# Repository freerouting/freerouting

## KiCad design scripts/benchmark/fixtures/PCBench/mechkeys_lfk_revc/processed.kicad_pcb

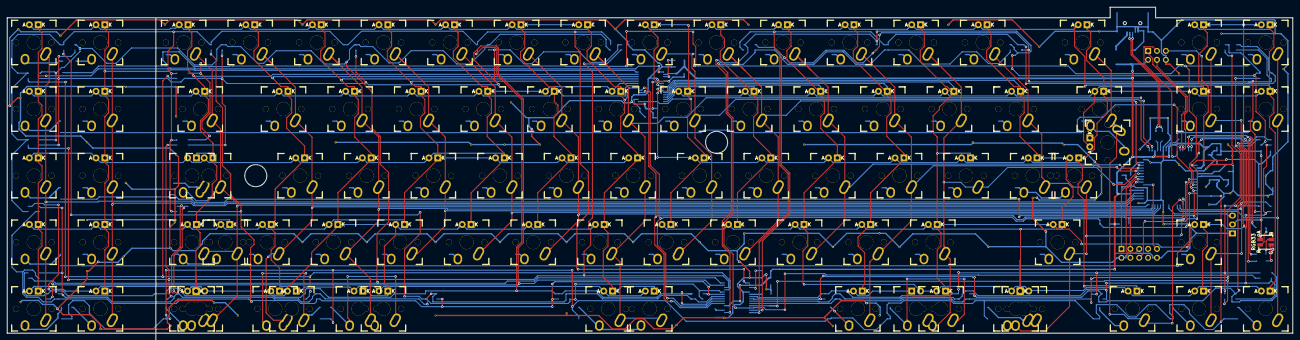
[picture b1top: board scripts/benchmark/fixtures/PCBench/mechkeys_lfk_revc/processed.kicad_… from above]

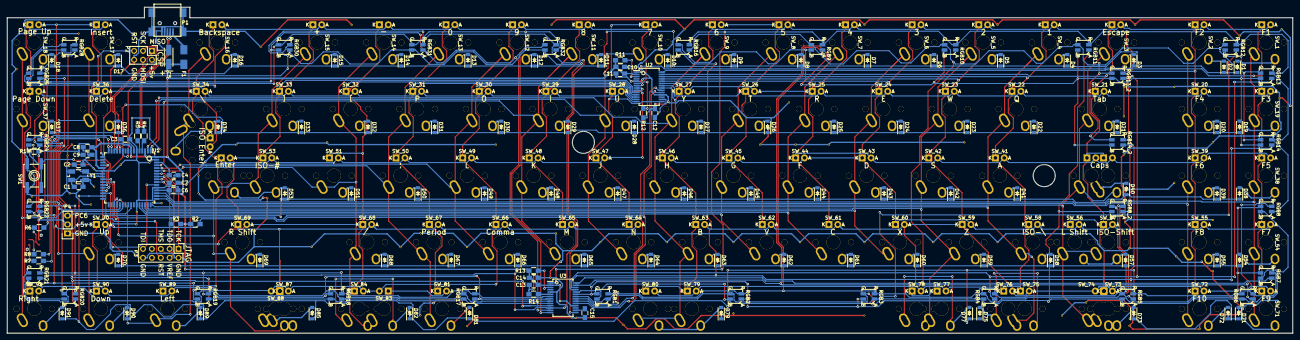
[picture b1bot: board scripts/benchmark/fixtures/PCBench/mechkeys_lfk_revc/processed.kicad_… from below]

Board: 2 copper layers, 367.8 x 93.2 mm, 238 parts (146 on the bottom side), 172 nets.

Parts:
C1, C2: 18pF; C_0805_HandSoldering
C3, C6, C7, C8, C9, C11, C12, C14, C15: 0.1µF; C_0805_HandSoldering
C4, C10, C13: 1µF; C_0805_HandSoldering
C5: 4.7µF; TantalC_SizeA_EIA-3216_HandSoldering
D1, D2, D3, D4, D5, D6, D7, D8, D9, D10, D11, D12, D13, D14, D15, D16, D17, D18, D19, D20, D21, D22, D23, D24, D25, D26, D27, D28, D29, D30, D31, D32, D33, D34, D36, D37, D38, D39, D40, D41, D42, D43, D44, D45, D46, D47, D48, D49, D50, D51, D53, D54, D55, D57, D58, D59, D60, D61, D62, D63, D64, D65, D66, D67, D68, D69, D70, D71, D72, D73, D75, D77, D79, D81, D82, D85, D89, D90, D91: D; SOD-123
F1: FP_Small; Fuse_SMD1206_HandSoldering
P1: USB_B; USB_Mini-B
P2: CONN_02X03; Pin_Header_Straight_2x03
P3: CONN_02X05; Pin_Header_Straight_2x05
P4: CONN_01X03; Pin_Header_Straight_1x03
R1: 10kΩ; R_0805_HandSoldering
R2, R3: 4.7kΩ; R_0805_HandSoldering
R4, R5: 22Ω; R_0805_HandSoldering
R6: 150; R_0805_HandSoldering
R7, R8: 120; R_0805_HandSoldering
R11, R13: 10KΩ; R_0805_HandSoldering
R12, R14: 20KΩ; R_0805_HandSoldering
RGB1, RGB2, RGB3, RGB4, RGB5, RGB6, RGB7, RGB8, RGB8_2, RGB9, RGB10, RGB11, RGB12, RGB13, RGB13_2, RGB14, RGB14_2, RGB16, RGB17, RGB18, RGB19, RGB20, RGB21, RGB22, RGB24, RGB25, RGB28, RGB30, RGB31, RGB32: Led_RGB_CA; SMP4-RGB
RGB33: Led_RGB_CA; SMP4-RGB-PIPE
STA: Stabilizer; CHERRY_PCB_200_STABILIZER_OUTLINE
STA_2: Stabilizer; CHERRY_PCB_200_STABILIZER_OUTLINE
SW1: SW_PUSH; SW_SPST_EVQP0
SW_1, SW_2, SW_3, SW_4, SW_5, SW_6, SW_7, SW_8, SW_9, SW_10, SW_11, SW_12, SW_13, SW_14, SW_15, SW_16, SW_17, SW_18, SW_19, SW_20, SW_21, SW_22, SW_23, SW_24, SW_25, SW_26, SW_27, SW_28, SW_29, SW_30, SW_31, SW_32, SW_33, SW_34, SW_35, SW_36, SW_37, SW_38, SW_39, SW_40, SW_40_2, SW_41, SW_42, SW_43, SW_44, SW_45, SW_46, SW_47, SW_48, SW_49, SW_50, SW_51, SW_52, SW_53, SW_54, SW_55, SW_56, SW_57, SW_58, SW_59, SW_60, SW_61, SW_62, SW_63, SW_64, SW_65, SW_66, SW_67, SW_68, SW_69, SW_70, SW_71, SW_72, SW_73, SW_75, SW_76, SW_77, SW_78, SW_79, SW_80, SW_81, SW_84, SW_87, SW_89, SW_90, SW_91: MX_LED; MXALPS
SW_74, SW_83, SW_88: MX_LED; MXALPS_REVERSE_LED
U1: AT90USB1286; TQFP-64_14x14mm_Pitch0.8mm
U2, U3: IS31FL3731; SSOP-28_5.3x10.2mm_Pitch0.65mm
Y1: 16Mhz; Crystal_SMD_5032_4Pads

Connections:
+5V: C5.1, C6.1, C7.1, C8.1, C9.1, C10.1, C11.1, C13.1, C14.1, F1.2, P2.2, P3.4, P4.2, R1.1, R2.1, R3.1, R11.2, R13.2, RGB33.1, U1.3, U1.8, U1.21, U1.52, U1.64, U2.2, U3.2, U3.18
AUDIO: P4.3, U1.41
C1: SW_1.SW1, SW_19.SW1, SW_38.SW1, SW_54.SW1, SW_71.SW1, U1.51
C2: SW_2.SW1, SW_20.SW1, SW_39.SW1, SW_55.SW1, SW_72.SW1, U1.50
C3: SW_3.SW1, SW_21.SW1, SW_40.SW1, SW_40_2.SW2, SW_56.SW1, SW_57.SW1, SW_73.SW1, SW_74.SW1, U1.49
C4: SW_4.SW1, SW_22.SW1, SW_41.SW1, SW_58.SW1, SW_75.SW1, SW_76.SW2, U1.48
C5: SW_5.SW1, SW_23.SW1, SW_42.SW1, SW_59.SW1, SW_77.SW1, SW_78.SW2, U1.47
C6: SW_6.SW1, SW_24.SW1, SW_43.SW1, SW_60.SW1, U1.46
C7: SW_7.SW1, SW_25.SW1, SW_44.SW1, SW_61.SW1, U1.45
C8: SW_8.SW1, SW_26.SW1, SW_45.SW1, SW_62.SW1, U1.44
C9: SW_9.SW1, SW_27.SW1, SW_46.SW1, SW_63.SW1, SW_79.SW1, SW_80.SW1, U1.1
C10: SW_10.SW1, SW_28.SW1, SW_47.SW1, SW_64.SW1, U1.2
C11: SW_11.SW1, SW_29.SW1, SW_48.SW1, SW_65.SW1, U1.61
C12: SW_12.SW1, SW_30.SW1, SW_49.SW1, SW_66.SW1, U1.60
C13: SW_13.SW1, SW_31.SW1, SW_50.SW1, SW_67.SW1, SW_81.SW1, U1.59
C14: SW_14.SW1, SW_32.SW1, SW_51.SW1, SW_68.SW1, SW_83.SW1, SW_84.SW2, U1.58
C15: SW_15.SW1, SW_33.SW1, SW_52.SW1, SW_53.SW1, SW_69.SW1, SW_87.SW2, SW_88.SW2, U1.35
C16: SW_16.SW1, SW_34.SW1, SW_35.SW1, SW_89.SW1, U1.36
C17: SW_17.SW1, SW_36.SW1, SW_70.SW1, SW_90.SW1, U1.37
C18: SW_18.SW1, SW_37.SW1, SW_91.SW1, U1.38
D+: R5.1, U1.5
D-: R4.1, U1.4
GND: C1.2, C2.2, C3.2, C4.2, C5.2, C6.2, C7.2, C8.2, C9.2, C10.2, C11.2, C12.2, C13.2, C14.2, C15.2, P1.4, P1.5, P1.6, P2.6, P3.2, P3.10, P4.1, R12.2, R14.2, SW1.1, U1.6, U1.22, U1.43, U1.53, U1.63, U2.5, U2.18, U3.5, Y1.3
LED_SCL: R2.2, U1.25, U2.20, U3.20
LED_SDA: R3.2, U1.26, U2.19, U3.19
L_CA1: SW_1.A, SW_2.A, SW_3.A, SW_4.A, SW_5.A, SW_6.A, SW_7.A, SW_8.A, SW_9.K, SW_27.K, SW_46.K, SW_63.K, SW_79.K, SW_80.K, U2.21
L_CA2: SW_8.K, SW_9.A, SW_19.A, SW_20.A, SW_21.A, SW_22.A, SW_23.A, SW_24.A, SW_25.A, SW_26.K, SW_45.K, SW_62.K, U2.22
L_CA3: SW_7.K, SW_25.K, SW_26.A, SW_27.A, SW_38.A, SW_39.A, SW_40.A, SW_40_2.A, SW_41.A, SW_42.A, SW_43.A, SW_44.K, SW_61.K, U2.23
L_CA4: SW_6.K, SW_24.K, SW_43.K, SW_44.A, SW_45.A, SW_46.A, SW_54.A, SW_55.A, SW_56.A, SW_57.A, SW_58.A, SW_59.A, SW_60.K, U2.24
L_CA5: SW_5.K, SW_23.K, SW_42.K, SW_59.K, SW_60.A, SW_61.A, SW_62.A, SW_63.A, SW_71.A, SW_72.A, SW_73.A, SW_74.A, SW_75.A, SW_76.A, SW_77.K, SW_78.K, U2.25
L_CA6: SW_4.K, SW_22.K, SW_41.K, SW_58.K, SW_75.K, SW_76.K, SW_77.A, SW_78.A, SW_79.A, SW_80.A, U2.26
L_CA7: SW_3.K, SW_21.K, SW_40.K, SW_40_2.K, SW_56.K, SW_57.K, SW_73.K, SW_74.K, U2.27
L_CA8: SW_2.K, SW_20.K, SW_39.K, SW_55.K, SW_72.K, U2.28
L_CA9: SW_1.K, SW_19.K, SW_38.K, SW_54.K, SW_71.K, U2.1
L_CB1: SW_10.A, SW_11.A, SW_12.A, SW_13.A, SW_14.A, SW_15.A, SW_16.A, SW_17.A, SW_18.K, SW_37.K, SW_91.K, U2.7
L_CB2: SW_17.K, SW_18.A, SW_28.A, SW_29.A, SW_30.A, SW_31.A, SW_32.A, SW_33.A, SW_34.A, SW_35.A, SW_36.K, SW_70.K, SW_90.K, U2.8
L_CB3: SW_16.K, SW_34.K, SW_35.K, SW_36.A, SW_37.A, SW_47.A, SW_48.A, SW_49.A, SW_50.A, SW_51.A, SW_52.K, SW_53.A, SW_89.K, U2.9
L_CB4: SW_15.K, SW_33.K, SW_52.A, SW_53.K, SW_64.A, SW_65.A, SW_66.A, SW_67.A, SW_68.A, SW_69.K, SW_87.K, SW_88.K, U2.10
L_CB5: SW_14.K, SW_32.K, SW_51.K, SW_68.K, SW_69.A, SW_70.A, SW_81.A, SW_83.K, SW_84.K, U2.11
L_CB6: SW_13.K, SW_31.K, SW_50.K, SW_67.K, SW_81.K, U2.12
L_CB7: SW_12.K, SW_30.K, SW_49.K, SW_66.K, SW_83.A, SW_84.A, SW_87.A, SW_88.A, SW_89.A, SW_90.A, SW_91.A, U2.13
L_CB8: SW_11.K, SW_29.K, SW_48.K, SW_65.K, U2.14
L_CB9: SW_10.K, SW_28.K, SW_47.K, SW_64.K, U2.15
MISO: P2.1, U1.13
MOSI: P2.4, U1.12
unnamed: C1.1, U1.24, Y1.1
unnamed: C2.1, U1.23, Y1.2
unnamed: C3.1, U1.7
unnamed: C4.1, U1.62
unnamed: C12.1, U2.16
unnamed: C15.1, U3.16
unnamed: D1.2, SW_1.SW2
unnamed: D2.2, SW_2.SW2
unnamed: D3.2, SW_3.SW2
unnamed: D4.2, SW_4.SW2
unnamed: D5.2, SW_5.SW2
unnamed: D6.2, SW_6.SW2
unnamed: D7.2, SW_7.SW2
unnamed: D8.2, SW_8.SW2
unnamed: D9.2, SW_9.SW2
unnamed: D10.2, SW_10.SW2
unnamed: D11.2, SW_11.SW2
unnamed: D12.2, SW_12.SW2
unnamed: D13.2, SW_13.SW2
unnamed: D14.2, SW_14.SW2
unnamed: D15.2, SW_15.SW2
unnamed: D16.2, SW_16.SW2
unnamed: D17.2, SW_17.SW2
unnamed: D18.2, SW_18.SW2
unnamed: D19.2, SW_19.SW2
unnamed: D20.2, SW_20.SW2
unnamed: D21.2, SW_21.SW2
unnamed: D22.2, SW_22.SW2
unnamed: D23.2, SW_23.SW2
unnamed: D24.2, SW_24.SW2
unnamed: D25.2, SW_25.SW2
unnamed: D26.2, SW_26.SW2
unnamed: D27.2, SW_27.SW2
unnamed: D28.2, SW_28.SW2
unnamed: D29.2, SW_29.SW2
unnamed: D30.2, SW_30.SW2
unnamed: D31.2, SW_31.SW2
unnamed: D32.2, SW_32.SW2
unnamed: D33.2, SW_33.SW2
unnamed: D34.2, SW_34.SW2, SW_35.SW2
unnamed: D36.2, SW_36.SW2
unnamed: D37.2, SW_37.SW2
unnamed: D38.2, SW_38.SW2
unnamed: D39.2, SW_39.SW2
unnamed: D40.2, SW_40.SW2, SW_40_2.SW1
unnamed: D41.2, SW_41.SW2
unnamed: D42.2, SW_42.SW2
unnamed: D43.2, SW_43.SW2
unnamed: D44.2, SW_44.SW2
unnamed: D45.2, SW_45.SW2
unnamed: D46.2, SW_46.SW2
unnamed: D47.2, SW_47.SW2
unnamed: D48.2, SW_48.SW2
unnamed: D49.2, SW_49.SW2
unnamed: D50.2, SW_50.SW2
unnamed: D51.2, SW_51.SW2
unnamed: D53.2, SW_52.SW2, SW_53.SW2
unnamed: D54.2, SW_54.SW2
unnamed: D55.2, SW_55.SW2
unnamed: D57.2, SW_56.SW2, SW_57.SW2
unnamed: D58.2, SW_58.SW2
unnamed: D59.2, SW_59.SW2
unnamed: D60.2, SW_60.SW2
unnamed: D61.2, SW_61.SW2
unnamed: D62.2, SW_62.SW2
unnamed: D63.2, SW_63.SW2
unnamed: D64.2, SW_64.SW2
unnamed: D65.2, SW_65.SW2
unnamed: D66.2, SW_66.SW2
unnamed: D67.2, SW_67.SW2
unnamed: D68.2, SW_68.SW2
unnamed: D69.2, SW_69.SW2
unnamed: D70.2, SW_70.SW2
unnamed: D71.2, SW_71.SW2
unnamed: D72.2, SW_72.SW2
unnamed: D73.2, SW_73.SW2, SW_74.SW2
unnamed: D75.2, SW_75.SW2, SW_76.SW1
unnamed: D77.2, SW_77.SW2, SW_78.SW1
unnamed: D79.2, SW_79.SW2, SW_80.SW2
unnamed: D81.2, SW_81.SW2
unnamed: D82.2, SW_83.SW2, SW_84.SW1
unnamed: D85.2, SW_87.SW1, SW_88.SW1
unnamed: D89.2, SW_89.SW2
unnamed: D90.2, SW_90.SW2
unnamed: D91.2, SW_91.SW2
unnamed: F1.1, P1.1
unnamed: R6.1, RGB33.2
unnamed: R7.1, RGB33.3
unnamed: R8.1, RGB33.4
unnamed: R11.1, U2.3
unnamed: R12.1, U2.6
unnamed: R13.1, U3.3
unnamed: R14.1, U3.6
PWM_BLUE: R8.2, U1.17
PWM_GREEN: R7.2, U1.16
PWM_RED: R6.2, U1.15
R1: D1.1, D2.1, D3.1, D4.1, D5.1, D6.1, D7.1, D8.1, D9.1, D10.1, D11.1, D12.1, D13.1, D14.1, D15.1, D16.1, D17.1, D18.1, U1.27
R2: D19.1, D20.1, D21.1, D22.1, D23.1, D24.1, D25.1, D26.1, D27.1, D28.1, D29.1, D30.1, D31.1, D32.1, D33.1, D34.1, D36.1, D37.1, U1.28
R3: D38.1, D39.1, D40.1, D41.1, D42.1, D43.1, D44.1, D45.1, D46.1, D47.1, D48.1, D49.1, D50.1, D51.1, D53.1, U1.29
R4: D54.1, D55.1, D57.1, D58.1, D59.1, D60.1, D61.1, D62.1, D63.1, D64.1, D65.1, D66.1, D67.1, D68.1, D69.1, D70.1, U1.30
R5: D71.1, D72.1, D73.1, D75.1, D77.1, D79.1, D81.1, D82.1, D85.1, D89.1, D90.1, D91.1, U1.31
RESET: P2.5, P3.6, R1.2, SW1.2, U1.20
R_CA1: RGB1.2, RGB2.2, RGB3.2, RGB4.2, RGB5.2, RGB6.2, RGB7.2, RGB8.2, RGB8_2.2, RGB9.1, U3.21
R_CA2: RGB1.1, RGB2.3, RGB3.3, RGB4.3, RGB5.3, RGB6.3, RGB7.3, RGB8.3, RGB8_2.3, U3.22
R_CA3: RGB1.3, RGB2.1, RGB3.4, RGB4.4, RGB5.4, RGB6.4, RGB7.4, RGB8.4, RGB8_2.4, RGB11.1, U3.23
R_CA4: RGB1.4, RGB2.4, RGB3.1, RGB12.1, U3.24
R_CA5: RGB4.1, RGB13.1, RGB13_2.1, U3.25
R_CA6: RGB5.1, RGB14.1, RGB14_2.1, RGB16.4, U3.26
R_CA7: RGB6.1, RGB9.4, RGB10.4, RGB11.4, RGB12.4, RGB13.4, RGB13_2.4, RGB14.4, RGB14_2.4, RGB16.3, U3.27
R_CA8: RGB7.1, RGB9.3, RGB10.3, RGB11.3, RGB12.3, RGB13.3, RGB13_2.3, RGB14.3, RGB14_2.3, RGB16.1, U3.28
R_CA9: RGB8.1, RGB8_2.1, RGB9.2, RGB10.2, RGB11.2, RGB12.2, RGB13.2, RGB13_2.2, RGB14.2, RGB14_2.2, RGB16.2, U3.1
R_CB1: RGB17.2, RGB18.2, RGB19.2, RGB20.2, RGB21.2, RGB22.2, RGB24.2, RGB25.1, U3.7
R_CB2: RGB17.1, RGB18.3, RGB19.3, RGB20.3, RGB21.3, RGB22.3, RGB24.3, U3.8
R_CB3: RGB17.3, RGB18.1, RGB19.4, RGB20.4, RGB21.4, RGB22.4, RGB24.4, U3.9
R_CB4: RGB17.4, RGB18.4, RGB19.1, RGB28.1, U3.10
R_CB5: RGB20.1, U3.11
R_CB6: RGB21.1, RGB30.1, RGB31.4, RGB32.4, U3.12
R_CB7: RGB22.1, RGB25.4, RGB28.4, RGB30.4, RGB31.1, RGB32.3, U3.13
R_CB8: RGB25.3, RGB28.3, RGB30.3, RGB31.3, RGB32.1, U3.14
R_CB9: RGB24.1, RGB25.2, RGB28.2, RGB30.2, RGB31.2, RGB32.2, U3.15
SCK: P2.3, U1.11
TCK: P3.1, U1.57
TDI: P3.9, U1.54
TDO: P3.3, U1.55
TMS: P3.5, U1.56
USB+: P1.3, R5.2
USB-: P1.2, R4.2

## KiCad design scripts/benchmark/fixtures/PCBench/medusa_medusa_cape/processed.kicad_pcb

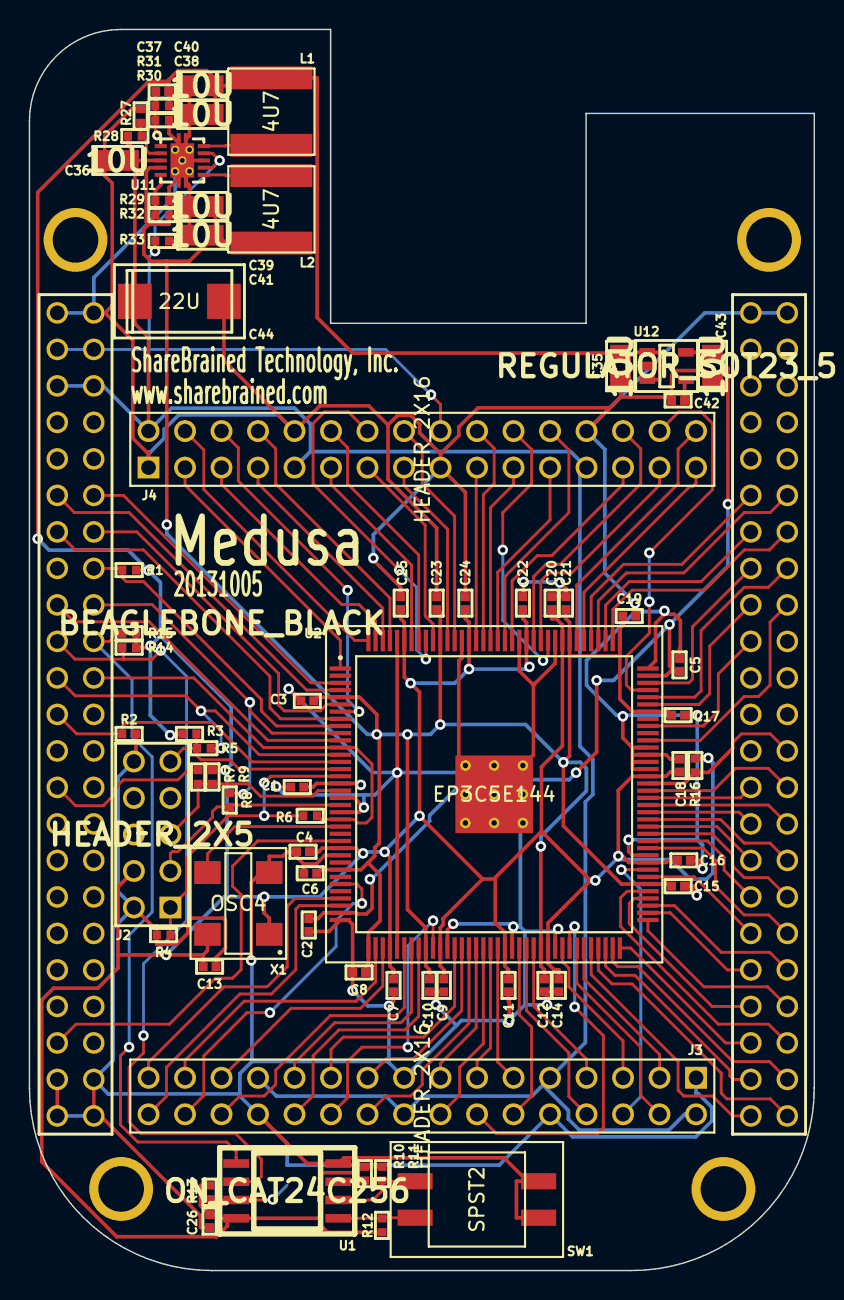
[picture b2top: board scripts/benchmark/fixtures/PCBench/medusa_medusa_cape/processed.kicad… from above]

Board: 4 copper layers, 54.6 x 86.4 mm, 73 parts (0 on the bottom side), 113 nets.

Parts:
C1, C2, C3, C4, C5, C6, C7, C8, C9, C10, C11, C12, C13, C14, C15, C16, C17, C18, C19, C20, C21, C22, C23, C24, C25, C26: 100N; IPC_CAPC1005X55N
C35, C36, C38, C39, C40, C41, C43: 10U; IPC_CAPC2012X140N
C37: 33P; IPC_CAPC1005X55N
C42: DNI; IPC_CAPC1005X55N
C44: 22U; IPC_CAPMP7343X310N
J1: BEAGLEBONE_BLACK; beaglebone_black
J2: HEADER_2X5; HEADER_5X2_TH_254
J3, J4: HEADER_2X16; HEADER_16X2_TH_254
L1, L2: 4U7; NR6028
R1, R2, R3, R9, R10, R11, R12, R13, R14, R15, R16, R28, R33: 10K; IPC_RESC1005X40N
R4: 1K; IPC_RESC1005X40N
R5, R6, R7, R8, R27: DNI; IPC_RESC1005X40N
R29, R30, R31, R32: R; IPC_RESC1005X40N
SW1: SPST2; 219-2MST
TP1, TP2: TP; TP_1MM
U1: ON_CAT24C256; IPC_SOIC127P780X205-8N
U2: EP3C5E144; QFP50P2200X2200X160-145N_ALTERA
U11: TPS62420; TI_DRC_S-PVSON-N10
U12: REGULATOR_SOT23_5; IPC_SOT95P280X110-5N
X1: OSC4; OSCSC508P500X700X180-4N

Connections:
+1.2V: C3.1, C6.1, C8.1, C10.1, C12.1, C15.1, C17.1, C19.1, C21.1, C23.1, C39.2, C41.2, L2.2, R32.2, U2.5, U2.29, U2.37, U2.45, U2.61, U2.78, U2.102, U2.109, U2.116, U2.134, U11.4
+2.5V: C2.1, C5.1, C43.1, U2.35, U2.107, U12.5
+3.3V: C1.1, C4.1, C7.1, C9.1, C11.1, C13.1, C14.1, C16.1, C18.1, C20.1, C22.1, C24.1, C25.1, C26.1, C35.1, C37.2, C38.1, C40.1, J2.4, L1.1, R1.1, R3.1, R9.1, R10.1, R11.1, R12.1, R13.1, R14.1, R15.1, R16.1, R31.2, U1.8, U2.17, U2.26, U2.40, U2.47, U2.56, U2.62, U2.81, U2.93, U2.117, U2.122, U2.130, U2.139, U12.1, U12.3, X1.1, X1.4
/FPGA/AF0: J3.3, U2.67
/FPGA/AF1: J3.4, U2.66
/FPGA/AF2: J3.5, U2.64
/FPGA/AF3: J3.7, U2.60
/FPGA/AF4: J3.8, U2.59
/FPGA/AF5: J3.11, U2.55
/FPGA/AF6: J3.12, U2.58
/FPGA/AF7: J3.13, U2.54
/FPGA/AF8: J3.15, U2.52
/FPGA/AF9: J3.16, U2.53
/FPGA/AF10: J3.19, U2.50
/FPGA/AF11: J3.20, U2.51
/FPGA/AF12: J3.21, U2.49
/FPGA/AF13: J3.23, U2.43
/FPGA/AF14: J3.24, U2.44
/FPGA/AF15: J3.27, U2.39
/FPGA/AF16: J3.28, U2.42
/FPGA/AF17: J3.29, U2.38
/FPGA/AF18: J3.31, U2.33
/FPGA/AF19: J3.32, U2.34
/FPGA/AS0: J3.6, U2.80
/FPGA/AS1: J3.14, U2.65
/FPGA/AS2: J3.22, U2.46
/FPGA/AS3: J3.30, U2.31
/FPGA/BF0: J4.3, U2.1
/FPGA/BF1: J4.4, U2.144
/FPGA/BF2: J4.5, U2.143
/FPGA/BF3: J4.7, U2.142
/FPGA/BF4: J4.8, U2.141
/FPGA/BF5: J4.11, U2.138
/FPGA/BF6: J4.12, U2.137
/FPGA/BF7: J4.13, U2.135
/FPGA/BF8: J4.15, U2.133
/FPGA/BF9: J4.16, U2.132
/FPGA/BF10: J4.19, U2.129
/FPGA/BF11: J4.20, U2.128
/FPGA/BF12: J4.21, U2.127
/FPGA/BF13: J4.23, U2.126
/FPGA/BF14: J4.24, U2.125
/FPGA/BF15: J4.27, U2.124
/FPGA/BF16: J4.28, U2.121
/FPGA/BF17: J4.29, U2.120
/FPGA/BF18: J4.31, U2.114
/FPGA/BF19: J4.32, U2.115
/FPGA/BS0: J4.6, U2.7
/FPGA/BS1: J4.14, U2.136
/FPGA/BS2: J4.22, U2.119
/FPGA/BS3: J4.30, U2.105
/FPGA/CLKOUT2: J1.B41, U2.25
/FPGA/EHRPWM1A: J1.B14, U2.6
/FPGA/EHRPWM1B: J1.B16, R1.2, U2.9
/FPGA/GPIO1_17: J1.B23, R2.1, U2.14
/FPGA/GPIO1_28: J1.B12, U2.3
/FPGA/GPIO1_29: J1.A26, R16.2, U2.92
/FPGA/GPIO2_1: J1.A18, U2.98
/FPGA/GPIO3_19: J1.B27, R7.2
/FPGA/I2C2_SCL: J1.B19, R14.2, U1.6
/FPGA/I2C2_SDA: J1.B20, R15.2, U1.5
/FPGA/LCD_DATA0: J1.A45, U2.68
/FPGA/LCD_DATA1: J1.A46, U2.69
/FPGA/LCD_DATA2: J1.A43, U2.70
/FPGA/LCD_DATA3: J1.A44, U2.71
/FPGA/LCD_DATA4: J1.A41, U2.72
/FPGA/LCD_DATA5: J1.A42, U2.77
/FPGA/LCD_DATA6: J1.A39, U2.76
/FPGA/LCD_DATA7: J1.A40, U2.73
/FPGA/LCD_DATA8: J1.A37, U2.74
/FPGA/LCD_DATA9: J1.A38, U2.75
/FPGA/LCD_DATA10: J1.A36, U2.83
/FPGA/LCD_DATA11: J1.A34, U2.85
/FPGA/LCD_DATA12: J1.A35, U2.79
/FPGA/LCD_DATA13: J1.A33, U2.84
/FPGA/LCD_DATA14: J1.A31, U2.86
/FPGA/LCD_DATA15: J1.A32, U2.87
/FPGA/LCD_DATA16: J1.A15, U2.106
/FPGA/LCD_DATA17: J1.A16, U2.104
/FPGA/LCD_DATA18: J1.A11, U2.113
/FPGA/LCD_DATA19: J1.A12, U2.112
/FPGA/LCD_DATA20: J1.A17, U2.103
/FPGA/LCD_DATA21: J1.A14, U2.110
/FPGA/LCD_DATA22: J1.A13, U2.111
/FPGA/LCD_DATA23: J1.A19, U2.100
/FPGA/LCD_DE: J1.A30, U2.89
/FPGA/LCD_HSYNC: J1.A29, U2.88
/FPGA/LCD_PCLK: J1.A28, U2.91
/FPGA/LCD_VSYNC: J1.A27, U2.90
/FPGA/PWREN: J1.B3, J1.B4, J4.18, R33.2, U11.7, U11.9
/FPGA/REF_CLK: U2.23, X1.3
/FPGA/SPI0_CS0: J1.B17, U2.11
/FPGA/SPI0_D0: J1.B21, R5.2, U2.13
/FPGA/SPI0_D1: J1.B18, R8.2, U2.10
/FPGA/SPI0_SCLK: J1.B22, R6.2, U2.12, U2.22
/FPGA/TCK: J2.1, R4.1, R6.1, U2.16
/FPGA/TDI: J2.9, R3.2, R5.1, U2.15
/FPGA/TDO: J2.3, R8.1, U2.20
/FPGA/TMS: J2.5, R7.1, R9.2, U2.18
/FPGA/UART4_RXD: J1.B11, U2.4
/FPGA/UART4_TXD: J1.B13, U2.8
/FPGA/V_RAW: C36.1, C44.1, J1.B5, J1.B6, J3.2, J3.9, J3.18, J3.25, J4.2, J4.9, J4.25, R28.1, U11.3
GND: C1.2, C2.2, C3.2, C4.2, C5.2, C6.2, C7.2, C8.2, C9.2, C10.2, C11.2, C12.2, C13.2, C14.2, C15.2, C16.2, C17.2, C18.2, C19.2, C20.2, C21.2, C22.2, C23.2, C24.2, C25.2, C26.2, C35.2, C36.2, C38.2, C39.1, C40.2, C41.1, C42.2, C43.2, C44.2, J1.A1, J1.A2, J1.B1, J1.B2, J1.B43, J1.B44, J1.B45, J1.B46, J2.2, J2.10, J3.1, J3.10, J3.17, J3.26, J4.1, J4.10, J4.17, J4.26, R2.2, R4.2, R27.1, R29.1, R30.1, R33.1, SW1.1, SW1.3, TP2.1, U1.4, U2.19, U2.21, U2.27, U2.36, U2.41, U2.48, U2.57, U2.63, U2.82, U2.94, U2.95, U2.96, U2.97, U2.108, U2.118, U2.123, U2.131, U2.140, U2.PAD, U11.0, U11.8, U12.2, X1.2
Net-<C37-Pad1>: C37.1, R30.2, R31.1, U11.1
Net-<C42-Pad1>: C42.1, U12.4
Net-<L1-Pad2>: L1.2, U11.10
Net-<L2-Pad1>: L2.1, U11.6
Net-<R10-Pad2>: R10.2, U1.3
Net-<R11-Pad2>: R11.2, SW1.4, U1.2
Net-<R12-Pad2>: R12.2, SW1.2, U1.1
Net-<R13-Pad2>: R13.2, TP1.1, U1.7
Net-<R27-Pad2>: R27.2, R28.2, U11.2
Net-<R29-Pad2>: R29.2, R32.1, U11.5
